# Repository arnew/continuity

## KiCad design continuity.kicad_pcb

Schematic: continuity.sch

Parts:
BAT1: Conn_01x02_Male; JST_XH_B2B-XH-A_1x02_P2.50mm_Vertical
C1, C2: 0.01uF; C_0805_2012Metric_Pad1.15x1.40mm_HandSolder
D2: S1J; D_SMA_Handsoldering
D3, D4: 1N4148; D_SOD-523
FID1, FID2: Fiducial; Fiducial_Modern_CopperTop
GREEN1: LED; LED_PLCC-2
GREEN2: Conn_01x02_Male; JST_XH_B2B-XH-A_1x02_P2.50mm_Vertical
H1, H2, H3, H4: MountingHole; MountingHole_3.2mm_M3
J3: Buchse Schwarz
J5: Buchse Rot
LS1: Speaker_Crystal; Buzzer_15x7.5RM7.6
LS2: Conn_01x02_Male; JST_XH_B2B-XH-A_1x02_P2.50mm_Vertical
N1: Testkabel
N2: Housing
N3: LED Fassung
NT1: Net-Tie_2; NetTie-2_SMD_Pad0.5mm
PROBE1: Conn_01x02_Male; JST_XH_B2B-XH-A_1x02_P2.50mm_Vertical
Q1: BCP52; SOT-223
Q2, Q3: BCP55; SOT-223
R2: 510; R_0603_1608Metric_Pad1.05x0.95mm_HandSolder
R3: 4,7k; R_0603_1608Metric_Pad1.05x0.95mm_HandSolder
R4, R6, R7, R8, R10: 10k; R_0603_1608Metric_Pad1.05x0.95mm_HandSolder
R5, R14, R15: 240; R_0603_1608Metric_Pad1.05x0.95mm_HandSolder
R9, R13: 500k; R_1206_3216Metric_Pad1.42x1.75mm_HandSolder
R11: 160; R_0603_1608Metric_Pad1.05x0.95mm_HandSolder
R12: 22k; R_0603_1608Metric_Pad1.05x0.95mm_HandSolder
RED1: LED; LED_PLCC-2
RED2: Conn_01x02_Male; JST_XH_B2B-XH-A_1x02_P2.50mm_Vertical
Ra1: 470; R_1206_3216Metric_Pad1.42x1.75mm_HandSolder
Rb1: 470; R_1206_3216Metric_Pad1.42x1.75mm_HandSolder
TBU1: TBU-CA050-050-WH; TBU
TP1: VCC; TestPoint_THTPad_1.0x1.0mm_Drill0.5mm
TP2: PROBE; TestPoint_THTPad_1.0x1.0mm_Drill0.5mm
TP3: SENSE; TestPoint_THTPad_1.0x1.0mm_Drill0.5mm
TP4: PROBE_uA; TestPoint_THTPad_1.0x1.0mm_Drill0.5mm
TP5: VCC_SW; TestPoint_THTPad_1.0x1.0mm_Drill0.5mm
TP6: KOMP_OUT; TestPoint_THTPad_1.0x1.0mm_Drill0.5mm
TP7: OUT; TestPoint_THTPad_1.0x1.0mm_Drill0.5mm
TP8: GND; TestPoint_THTPad_1.0x1.0mm_Drill0.5mm
U1: MCP 6V11T-EOT; SOT-23-5

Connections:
/KOMP_OUT: R7.1, R12.2, TP6.1, U1.1
/Probe: PROBE1.2, R9.2, TBU1.3, TP2.1
/Probe_uA: C2.1, D3.2 (A), D4.1 (K), R10.2, R13.1, TP4.1
/VCC: BAT1.2, D3.1 (K), LS1.1, LS2.2, Q1.3 (E), Ra1.1, Rb1.1, TP1.1
/VCC_SW: C1.1, GREEN1.2 (A), GREEN2.2, Q1.2 (C), Q1.4 (C), R4.2, R8.2, RED1.2 (A), RED2.2, TP5.1, U1.5
GND: BAT1.1, C1.2, C2.2, D4.2 (A), PROBE1.1, Q2.3 (E), Q3.3 (E), R5.1, R6.2, R11.1, TP8.1, U1.2
unnamed: D2.1 (K), TBU1.1
unnamed: D2.2 (A), NT1.1, Ra1.2, Rb1.2
unnamed: GREEN1.1 (K), GREEN2.1, R14.2
unnamed: LS1.2, LS2.1, R15.2
unnamed: NT1.2, R2.2
unnamed: Q1.1 (B), R2.1, R3.2, TP3.1
unnamed: Q2.1 (B), R4.1, R6.1
unnamed: Q2.2 (C), Q2.4 (C), R3.1
unnamed: Q3.1 (B), R7.2
unnamed: Q3.2 (C), Q3.4 (C), R14.1, R15.1, TP7.1
unnamed: R5.2, RED1.1 (K), RED2.1
unnamed: R10.1, U1.4
unnamed: R8.1, R11.2, R12.1, U1.3
unnamed: R9.1, R13.2

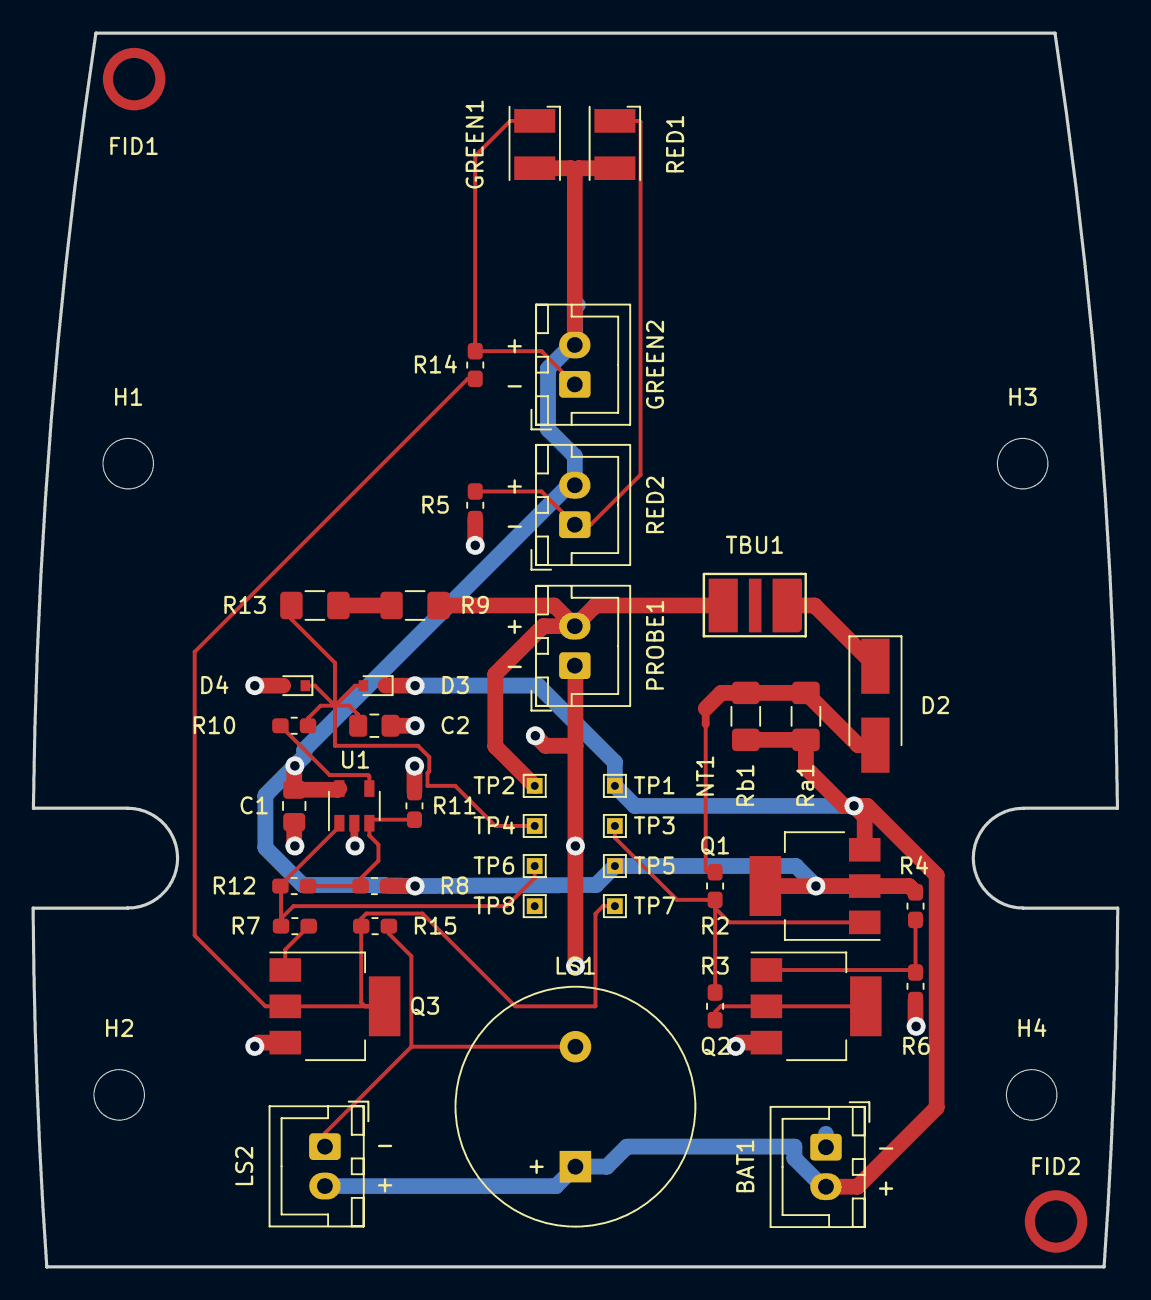
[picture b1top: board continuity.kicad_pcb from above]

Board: 2 copper layers, 68.7 x 78.2 mm, 49 parts (0 on the bottom side), 20 nets.

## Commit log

2020-07-17 init
2020-08-07 snap
